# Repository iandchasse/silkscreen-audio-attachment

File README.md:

# Silkscreen audio attachment

> [!IMPORTANT]
> **AI-generated design. This is an accessory, not part of the Silkscreen PCBA.**
>
> This audio attachment was designed with substantial AI assistance: its board and housing are generated by code
> written with AI tools. The Silkscreen PCBA itself ([silkscreen-pcb](https://github.com/iandchasse/silkscreen-pcb))
> was not AI-generated. See Silkscreen's AI disclosure: https://silkscreenreader.com/ai

**A clip-on headphone / line output for the [Silkscreen](https://github.com/iandchasse/silkscreen-pcb) e-reader.**
It is a small cap that pushes onto the top of the 4.26" case, the same way as the
[light attachment](https://github.com/iandchasse/silkscreen-light-attachment). Six header pins go down through the opening the case already has
in its top wall and plug into the main board's expansion header, the 12-pin socket on its top edge (`J6`). The case
is not modified. A 3.5 mm stereo jack sits at the cap's left end, as seen from the display side.

> **Status (2026-11-09): rev A, designed and checked in CAD. NOT built or tested.**
> - **Board:** passes ERC 0 and DRC 0 with schematic parity, plus its own pin-position, keep-out, silk and field gates.
> - **Printed parts:** pass every scripted fit check against the current 4.26" standard case.
> - **First article:** see [docs/ASSEMBLY.md](docs/ASSEMBLY.md) "First power-up". Meter the jack's tip/ring/sleeve
>   mapping before plugging in headphones.

## How it works
- **Signals:**
  - The e-reader sends audio as I2S on the expansion header's three spare GPIOs: bit clock on `IO46` (pin 2), data on
    `IO45` (pin 3), word select on `IO3` (pin 9).
  - No master clock, no I2C, no setup registers.
- **Audio path:** a TI **PCM5102A** DAC drives a TI **TPA6138A2** ground-centred headphone driver, which drives the
  jack (tip = left, ring = right, sleeve = ground).
  - About 40 mW into 32 Ω.
  - About 2 Vrms into a line input.
- **Power:**
  - It comes from the battery pin (pin 12) through a TI **TPS7A2033** 3.3 V regulator.
  - The regulator only turns on while audio is playing: a two-diode charge pump on the word-select line drives its
    enable pin.
  - When the e-reader stops sending audio, the headphone driver mutes after about 1 s and the whole board switches off
    after about 2-4 s.
  - Idle draw is about 0.1 µA. The board never uses the header's 3V3 pin, which is limited to 20 mA on Rev 1.03.
- **Draw while playing:** about 33 mA in silence, about 50 mA at normal headphone level, about 110 mA at full volume
  into 32 Ω.
- **Presence detect:** the firmware can tell whether the cap is fitted.
  - It turns on `IO3`'s internal pull-up and reads the pin. The cap's 10 kΩ pull-down (`R7`) makes it read LOW.
  - With no cap, or with the light attachment (which has no pin 9), it reads HIGH.
- **Firmware:** the e-reader firmware needs I2S output added; it is not in the current firmware.
  - See [docs/FIRMWARE-NOTES.md](docs/FIRMWARE-NOTES.md) for the settings, the presence check and a tone-test example.
  - An existing CrossPoint fork already has an audio player (MP3, FLAC, AAC, Opus...) that can be ported with a few
    changes. [research/software.md](research/software.md) covers it, along with text-to-speech options and what the
    output should sound like: about phone-headphone-jack quality, against the 16 kHz "phone call" sound of some other
    e-readers.
- **Bluetooth:** not on the board.
  - The ESP32-S3 can't send Bluetooth headphone audio itself.
  - The one no-firmware module found is unverified, and JLC can't assemble it.
  - **A battery-powered 3.5 mm Bluetooth transmitter plugged into the jack works today.** See
    [docs/BLUETOOTH-FOLLOWUP.md](docs/BLUETOOTH-FOLLOWUP.md).

## What you need
| Item | Qty | Notes |
|---|---|---|
| Audio PCBA | 1 | 2 layers, 1.0 mm, 65.0 × 13.0 mm. JLCPCB assembles the 42 SMD parts on the top side. See [docs/ORDERING.md](docs/ORDERING.md) |
| Pin header 1 × 4, 11.5 mm (Hong Cheng HC-PZ254-11.5L-1x4PZ) | 1 | [LCSC C27985189](https://www.lcsc.com/product-detail/C27985189.html), soldered by you (`J1`, pins 1-4) |
| Pin header 1 × 1, 11.5 mm (Hong Cheng HC-PZ254-11.5L-1x1PZ) | 2 | [LCSC C27985186](https://www.lcsc.com/product-detail/C27985186.html), soldered by you (`J2` on pin 9, `J3` on pin 12) |
| Printed base and lid | 1 each | PETG (PLA for a trial), no supports. Base 20 min 21 s / 3.25 g; lid 12 min 36 s / 3.39 g (OrcaSlicer, 0.4 nozzle, 0.20 mm). Turn on "Detect thin wall" so the 0.2 mm stop under each screw hole prints |
| M2 × 3 pan-head screws | 2 | No longer than 3 mm |

Any standard 2.54 mm breakaway male header with 11.5 mm pins also works for the headers: 6.0 mm mating side, 2.5 mm
body and 3.0 mm tail. These are the same pins as the light attachment uses. Snap a 1 × 4 and two 1 × 1 pieces off a
strip.

**Cost:** about $41 for 5 assembled boards at JLCPCB (about $8 each), before shipping. Most of a small order is JLC's
fixed fees (about $25). See [docs/ORDERING.md](docs/ORDERING.md).

## Safety
- **Only these header pins have metal:** 1 and 4 (ground), 2, 3, 9 (I2S) and 12 (battery). The light pins (5, 6, 11),
  3V3 (7) and I2C (8, 10) have nothing on this board.
- **Plug it in only with the cap assembled.** The cap keys the pins: it only fits one way, and turned round the pins
  land on solid plastic. A bare board can be pushed in wrongly and would put the battery pin on the wrong pins.
- **All three audio lines are ESP32-S3 boot strapping pins.** `IO45` held HIGH at reset stops the e-reader booting;
  `IO46` HIGH breaks download mode; `IO3` only matters if a JTAG eFuse is burned.
  - The board only pulls them LOW, which is the correct level: 100 kΩ on `IO45`/`IO46` and 10 kΩ on `IO3`.
  - Nothing on it can drive a line HIGH.
  - Still, run the boot check in [docs/ASSEMBLY.md](docs/ASSEMBLY.md) on a first board.
- **While USB charges and audio plays,** the charger can't finish charging, because the board draws more than its
  termination current. Charging finishes normally a few seconds after the audio stops.
- **Volume:** the hardware has no volume control. Start the firmware at about -30 dBFS for headphones.

## Folders
| Path | What |
|---|---|
| `pcb/` | Generated KiCad 9 project (`pcb/tools/` builds everything; don't hand-edit the `.kicad_*` files). Fab files in `pcb/production/` |
| `housing/` | CadQuery project for the base and lid, its fit checks and print files (`housing/out/print/`) |
| `design/DESIGN-SPEC.md` | The design contract and the decisions behind it |
| `research/` | Audio chain, power, Bluetooth and software research (existing firmware, libraries, TTS, sound quality); `basis/` holds the J6 and case notes from the light attachment |
| `docs/` | Ordering, assembly, firmware notes, Bluetooth follow-up |

## Regenerating
**Board** (close KiCad first):
```
cd pcb
"C:\Program Files\KiCad\9.0\bin\python.exe" tools\generate.py --reroute
"C:\Program Files\KiCad\9.0\bin\python.exe" tools\make_outputs.py
```
- `generate.py` places the parts and routes the board; that takes about 10 min, up to 40 seeded attempts, stopping at
  the first with 0 failures.
- `make_outputs.py` writes production files only if every gate passes.

**Housing**, with the enclosure project's venv (CadQuery, trimesh, manifold3d):
```
cd housing\src
"..\..\..\silkscreen-enclosure-claude\.venv\Scripts\python.exe" build.py
```
- It reads `pcb/build/geometry.json`, the E-frame PCBA STL, and the case meshes in
  `../silkscreen-enclosures/enclosures/case-426/out/standard` (override with `SILKSCREEN_CASE_OUT`).
- The 3.68" case has no expansion header and isn't supported.

## Licence
CERN-OHL-S v2; see [LICENSE](LICENSE) and [NOTICE](NOTICE).

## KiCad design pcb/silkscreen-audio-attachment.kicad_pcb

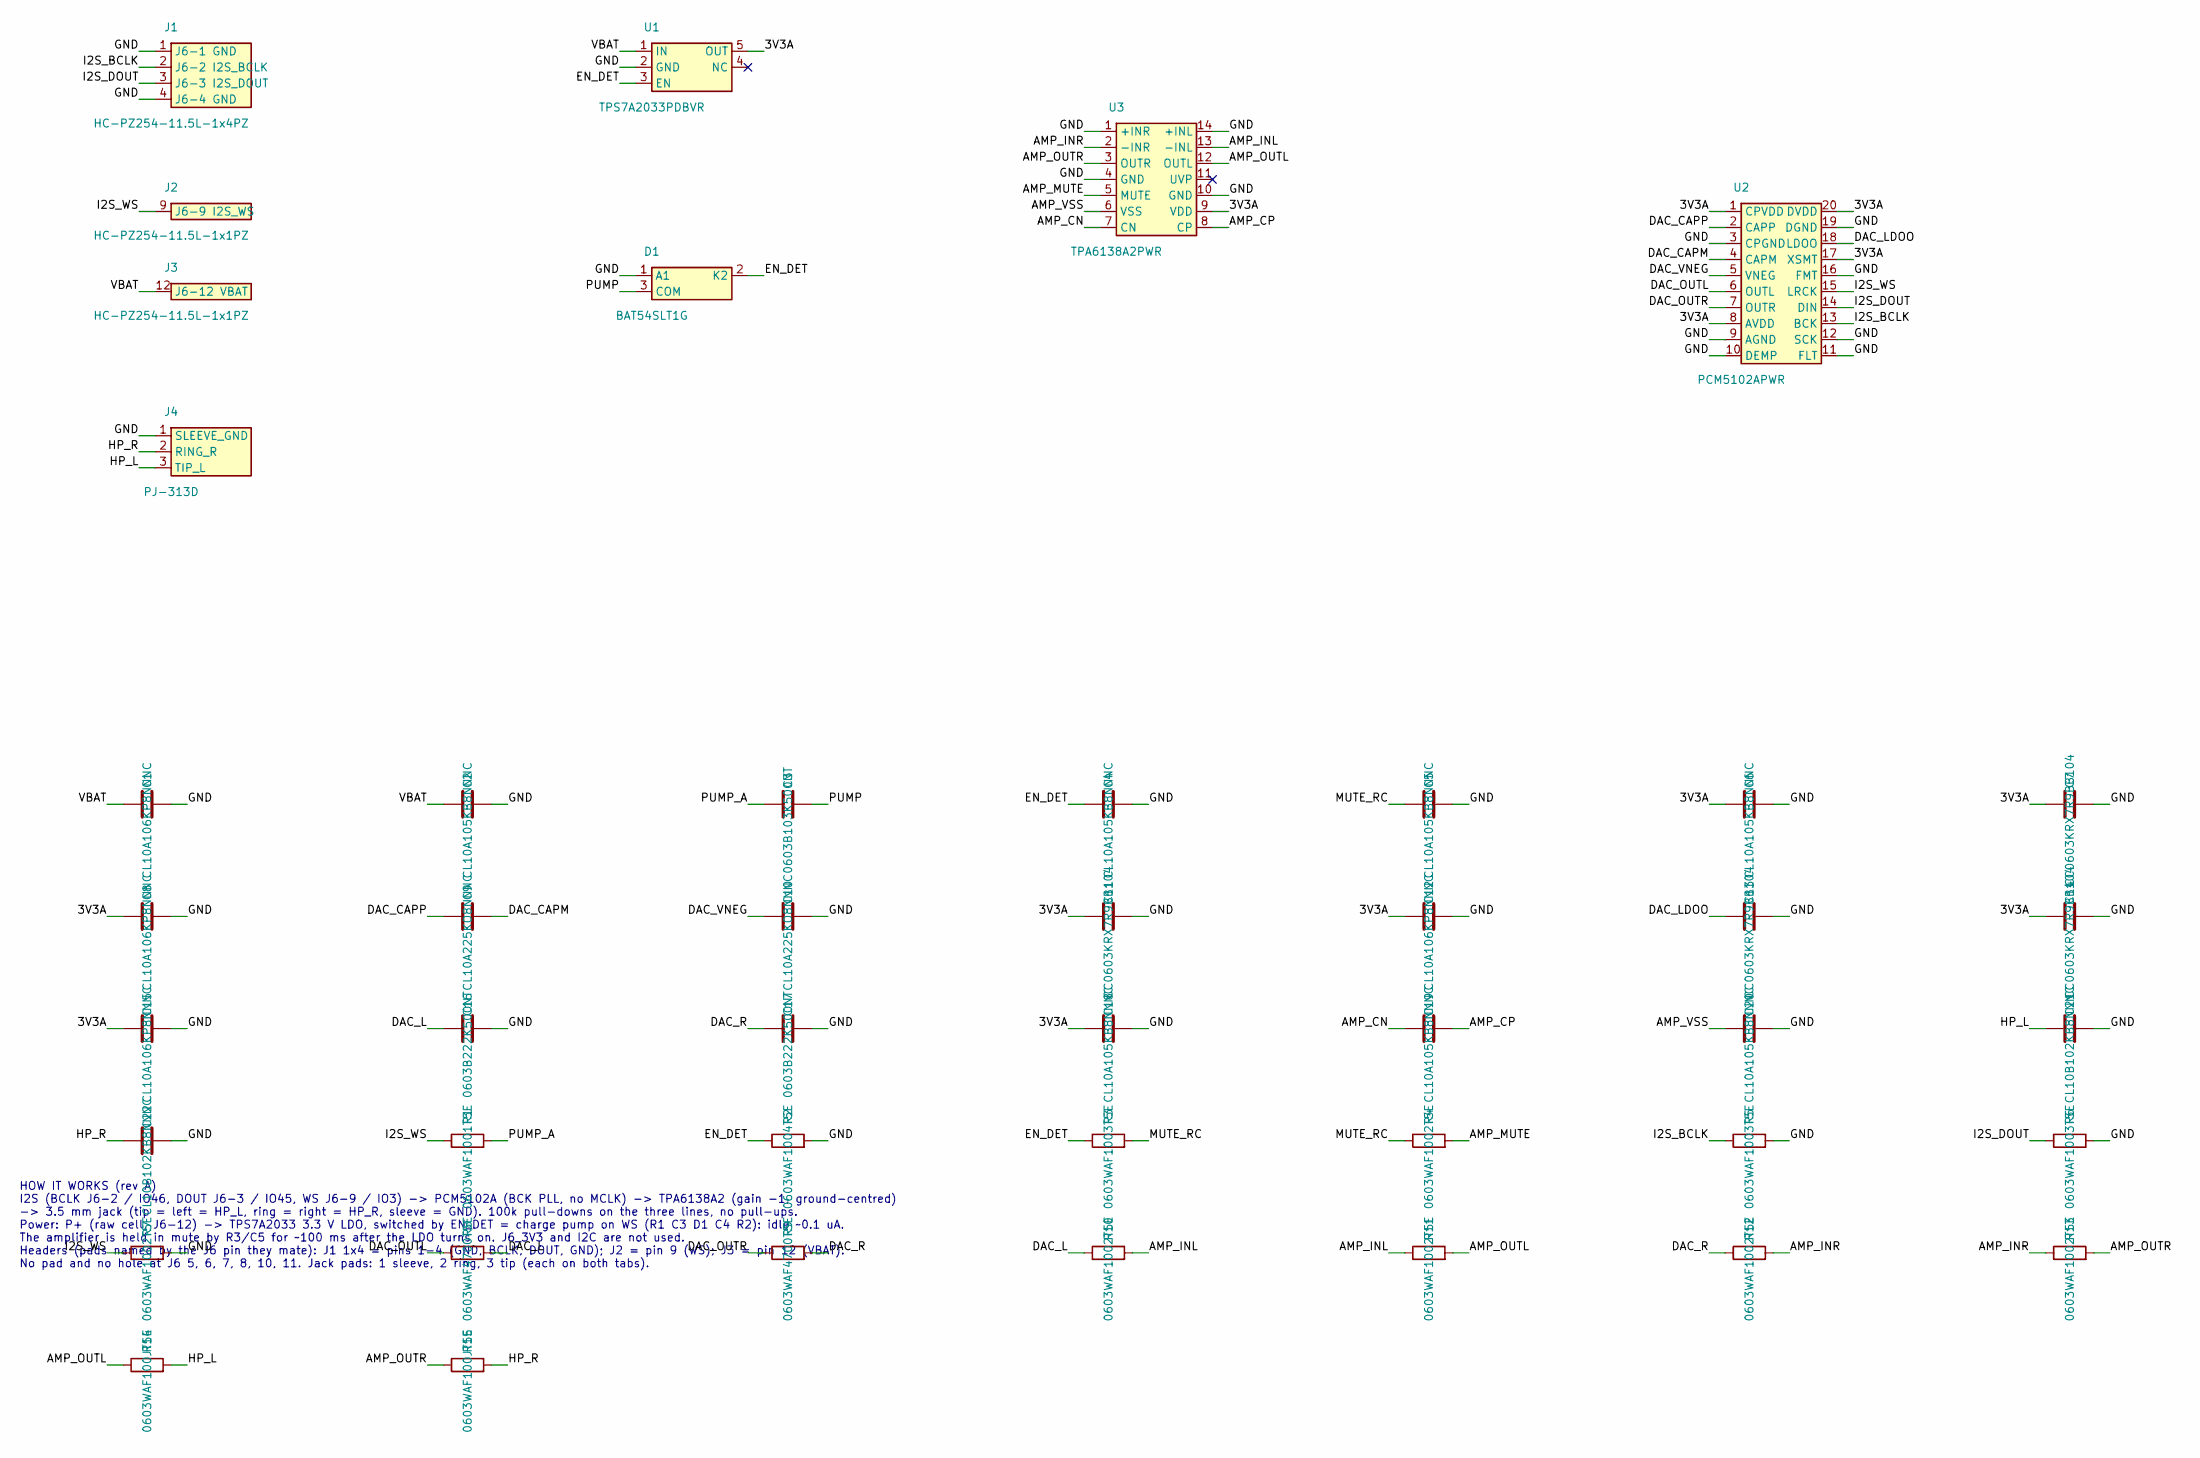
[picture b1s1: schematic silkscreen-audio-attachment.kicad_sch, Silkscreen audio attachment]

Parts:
C1, C8, C12, C15: CL10A106KP8NNNC; C_0603_1608Metric; MPN CL10A106KP8NNNC; DigiKey search DigiKey for CL10A106KP8NNNC (par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
C2, C4, C5, C6, C18, C19, C20: CL10A105KB8NNNC; C_0603_1608Metric; MPN CL10A105KB8NNNC; DigiKey search DigiKey for CL10A105KB8NNNC (par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
C3: 0603B103K500NT; C_0603_1608Metric; MPN 0603B103K500NT; DigiKey search DigiKey for 0603B103K500NT (part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
C7, C11, C13, C14: CC0603KRX7R9BB104; C_0603_1608Metric; MPN CC0603KRX7R9BB104; DigiKey search DigiKey for CC0603KRX7R9BB104 (p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
C9, C10: CL10A225KO8NNNC; C_0603_1608Metric; MPN CL10A225KO8NNNC; DigiKey search DigiKey for CL10A225KO8NNNC (par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
C16, C17: 0603B222K500NT; C_0603_1608Metric; MPN 0603B222K500NT; DigiKey search DigiKey for 0603B222K500NT (part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
C21, C22: CL10B102KB8NNNC; C_0603_1608Metric; MPN CL10B102KB8NNNC; DigiKey search DigiKey for CL10B102KB8NNNC (par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
D1: BAT54SLT1G; SOT-23; MPN BAT54SLT1G; DigiKey BAT54SLT1GOSCT-ND
J1: HC-PZ254-11.5L-1x4PZ; J6_PLUG_1x4_P1-P4; MPN HC-PZ254-11.5L-1x4PZ; DigiKey n/a - Hong Cheng is LCSC-only; DigiKey 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
J2: HC-PZ254-11.5L-1x1PZ; J6_PLUG_1x1_P9; MPN HC-PZ254-11.5L-1x1PZ; DigiKey 1 pin cut from a Harwin M20-999 series 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
J3: HC-PZ254-11.5L-1x1PZ; J6_PLUG_1x1_P12; MPN HC-PZ254-11.5L-1x1PZ; DigiKey 1 pin cut from a Harwin M20-999 series 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
J4: PJ-313D; JACK_3.5mm_SHOUHAN_PJ-313D; MPN PJ-313D; DigiKey none (LCSC only); DigiKey alternative w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
R1: 0603WAF1001T5E; R_0603_1608Metric; MPN 0603WAF1001T5E; DigiKey search DigiKey for 0603WAF1001T5E (part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
R2: 0603WAF1004T5E; R_0603_1608Metric; MPN 0603WAF1004T5E; DigiKey search DigiKey for 0603WAF1004T5E (part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
R3, R5, R6: 0603WAF1003T5E; R_0603_1608Metric; MPN 0603WAF1003T5E; DigiKey search DigiKey for 0603WAF1003T5E (part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
R4, R7, R10, R11, R12, R13: 0603WAF1002T5E; R_0603_1608Metric; MPN 0603WAF1002T5E; DigiKey search DigiKey for 0603WAF1002T5E (part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
R8, R9: 0603WAF4700T5E; R_0603_1608Metric; MPN 0603WAF4700T5E; DigiKey search DigiKey for 0603WAF4700T5E (part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
R14, R15: 0603WAF100JT5E; R_0603_1608Metric; MPN 0603WAF100JT5E; DigiKey search DigiKey for 0603WAF100JT5E (part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
U1: TPS7A2033PDBVR; SOT-23-5; MPN TPS7A2033PDBVR; DigiKey 296-TPS7A2033PDBVRCT-ND
U2: PCM5102APWR; TSSOP-20_4.4x6.5mm_P0.65mm; MPN PCM5102APWR; DigiKey 296-36707-1-ND
U3: TPA6138A2PWR; TSSOP-14_4.4x5mm_P0.65mm; MPN TPA6138A2PWR; DigiKey 296-28248-1-ND

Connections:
/3V3A: C6.1, C7.1, C8.1, C11.1, C12.1, C14.1, C15.1, C18.1, U1.5 (OUT), U2.1 (CPVDD), U2.8 (AVDD), U2.17 (XSMT), U2.20 (DVDD), U3.9 (VDD)
/AMP_CN: C19.1, U3.7 (CN)
/AMP_CP: C19.2, U3.8 (CP)
/AMP_INL: R10.2, R11.1, U3.13 (-INL)
/AMP_INR: R12.2, R13.1, U3.2 (-INR)
/AMP_MUTE: R4.2, U3.5 (MUTE)
/AMP_OUTL: R11.2, R14.1, U3.12 (OUTL)
/AMP_OUTR: R13.2, R15.1, U3.3 (OUTR)
/AMP_VSS: C20.1, U3.6 (VSS)
/DAC_CAPM: C9.2, U2.4 (CAPM)
/DAC_CAPP: C9.1, U2.2 (CAPP)
/DAC_L: C16.1, R8.2, R10.1
/DAC_LDOO: C13.1, U2.18 (LDOO)
/DAC_OUTL: R8.1, U2.6 (OUTL)
/DAC_OUTR: R9.1, U2.7 (OUTR)
/DAC_R: C17.1, R9.2, R12.1
/DAC_VNEG: C10.1, U2.5 (VNEG)
/EN_DET: C4.1, D1.2 (K2), R2.1, R3.1, U1.3 (EN)
/GND: C1.2, C2.2, C4.2, C5.2, C6.2, C7.2, C8.2, C10.2, C11.2, C12.2, C13.2, C14.2, C15.2, C16.2, C17.2, C18.2, C20.2, C21.2, C22.2, D1.1 (A1), J1.1 (J6-1 GND), J1.4 (J6-4 GND), J4.1 (SLEEVE_GND), R2.2, R5.2, R6.2, R7.2, U1.2 (GND), U2.3 (CPGND), U2.9 (AGND), U2.10 (DEMP), U2.11 (FLT), U2.12 (SCK), U2.16 (FMT), U2.19 (DGND), U3.1 (+INR), U3.4 (GND), U3.10 (GND), U3.14 (+INL)
/HP_L: C21.1, J4.3 (TIP_L), R14.2
/HP_R: C22.1, J4.2 (RING_R), R15.2
/I2S_BCLK: J1.2 (J6-2 I2S_BCLK), R5.1, U2.13 (BCK)
/I2S_DOUT: J1.3 (J6-3 I2S_DOUT), R6.1, U2.14 (DIN)
/I2S_WS: J2.9, R1.1, R7.1, U2.15 (LRCK)
/MUTE_RC: C5.1, R3.2, R4.1
/PUMP: C3.2, D1.3 (COM)
/PUMP_A: C3.1, R1.2
/VBAT: C1.1, C2.1, J3.12, U1.1 (IN)

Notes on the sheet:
HOW IT WORKS (rev A) I2S (BCLK J6-2 / IO46, DOUT J6-3 / IO45, WS J6-9 / IO3) -> PCM5102A (BCK PLL, no MCLK) -> TPA6138A2 (gain -1, ground-centred) -> 3.5 mm jack (tip = left = HP_L, ring = right = HP_R, sleeve = GND). 100k pull-downs on the three lines, no pull-ups. Power: P+ (raw cell, J6-12) -> T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

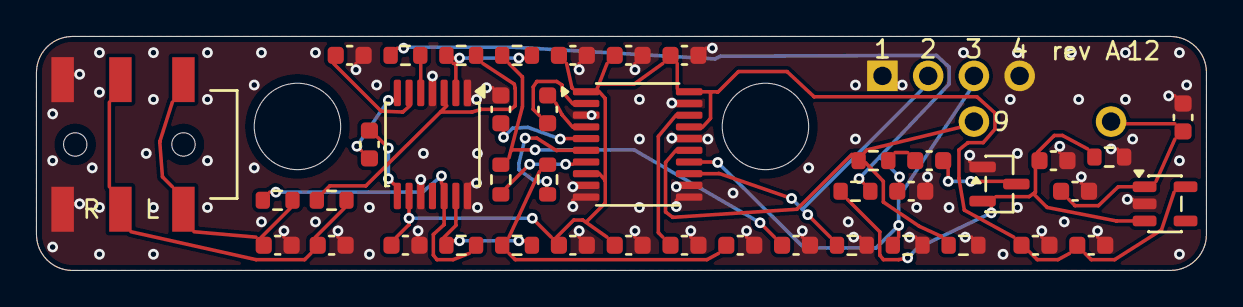
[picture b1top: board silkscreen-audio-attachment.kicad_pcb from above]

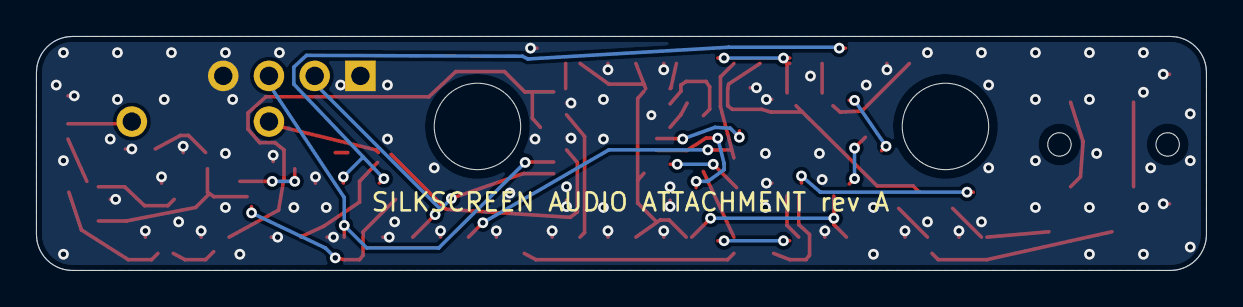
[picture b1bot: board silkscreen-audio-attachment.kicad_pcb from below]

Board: 2 copper layers, 65.0 x 13.0 mm, 47 parts (3 on the bottom side), 28 nets.

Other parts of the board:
H1: M1 lid screw column (rev C base, left boss moved 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; NPTH_4.80mm
H2: M2 lid screw column; NPTH_4.80mm

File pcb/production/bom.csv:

Qty,Refs,Value,Manufacturer,MPN,DigiKey,LCSC,JLC type,Footprint,Assembly,Description
4,"C1,C8,C12,C15",CL10A106KP8NNNC,Samsung Electro-Mechanics,CL10A106KP8NNNC,search DigiKey for CL10A106KP8NNNC (part number not verified),C19702,JLC Basic,C_0603_1608Metric,JLC SMT (top side),10 uF 10 V X5R 0603
7,"C2,C4,C5,C6,C18,C19,C20",CL10A105KB8NNNC,Samsung Electro-Mechanics,CL10A105KB8NNNC,search DigiKey for CL10A105KB8NNNC (part number not verified),C15849,JLC Basic,C_0603_1608Metric,JLC SMT (top side),1 uF 50 V X5R 0603
1,C3,0603B103K500NT,Fenghua (FH),0603B103K500NT,search DigiKey for 0603B103K500NT (part number not verified),C57112,JLC Basic,C_0603_1608Metric,JLC SMT (top side),10 nF 50 V X7R 0603
4,"C7,C11,C13,C14",CC0603KRX7R9BB104,Yageo,CC0603KRX7R9BB104,search DigiKey for CC0603KRX7R9BB104 (part number not verified),C14663,JLC Basic,C_0603_1608Metric,JLC SMT (top side),100 nF 50 V X7R 0603
2,"C9,C10",CL10A225KO8NNNC,Samsung Electro-Mechanics,CL10A225KO8NNNC,search DigiKey for CL10A225KO8NNNC (part number not verified),C23630,JLC Basic,C_0603_1608Metric,JLC SMT (top side),2.2 uF 16 V X5R 0603
2,"C16,C17",0603B222K500NT,Fenghua (FH),0603B222K500NT,search DigiKey for 0603B222K500NT (part number not verified),C1604,JLC Basic,C_0603_1608Metric,JLC SMT (top side),2.2 nF 50 V X7R 0603
2,"C21,C22",CL10B102KB8NNNC,Samsung Electro-Mechanics,CL10B102KB8NNNC,search DigiKey for CL10B102KB8NNNC (part number not verified),C1588,JLC Basic,C_0603_1608Metric,JLC SMT (top side),1 nF 50 V X7R 0603
1,D1,BAT54SLT1G,onsemi,BAT54SLT1G,BAT54SLT1GOSCT-ND,C8592,JLC Extended,SOT-23,JLC SMT (top side),"Dual Schottky diode, series pair, SOT-23. JLC/LCSC part: Jiangsu Changjing BAT54S (C8592)"
1,J1,HC-PZ254-11.5L-1x4PZ,Hong Cheng,HC-PZ254-11.5L-1x4PZ,"n/a - Hong Cheng is LCSC-only; DigiKey equivalent: Harwin M20-999 series 1x4 cut from a longer strip (6.1 mm post, 3 mm tail), part number not verified",C27985189,JLC Extended,J6_PLUG_1x4_P1-P4,"THT: JLC hand-solders it, or untick it at JLC and solder it yourself","1x4 2.54 mm straight male pin header, body 2.5, mating post 6.0, tail 3.0, 0.64 sq; mounted from the underside, soldered by the builder on the top side; pins = J6 1/2/3/4"
1,J2,HC-PZ254-11.5L-1x1PZ,Hong Cheng,HC-PZ254-11.5L-1x1PZ,"1 pin cut from a Harwin M20-999 series strip (6.1 mm post, 3 mm tail), part number not verified",C27985186,JLC Extended,J6_PLUG_1x1_P9,"THT: JLC hand-solders it, or untick it at JLC and solder it yourself","1x1 2.54 mm straight male pin header, body 2.5, mating post 6.0, tail 3.0, 0.64 sq; mounted from the underside, soldered by the builder on the top side; pins = J6 9"
1,J3,HC-PZ254-11.5L-1x1PZ,Hong Cheng,HC-PZ254-11.5L-1x1PZ,"1 pin cut from a Harwin M20-999 series strip (6.1 mm post, 3 mm tail), part number not verified",C27985186,JLC Extended,J6_PLUG_1x1_P12,"THT: JLC hand-solders it, or untick it at JLC and solder it yourself","1x1 2.54 mm straight male pin header, body 2.5, mating post 6.0, tail 3.0, 0.64 sq; mounted from the underside, soldered by the builder on the top side; pins = J6 12"
1,J4,PJ-313D,SHOU HAN,PJ-313D,none (LCSC only); DigiKey alternative with a different land: CUI SJ-3524-SMT-TR,C668608,JLC Extended,JACK_3.5mm_SHOUHAN_PJ-313D,JLC SMT (top side),"3.5 mm stereo headphone jack, SMD, 14 x 6 x 5 mm; pad 1 sleeve (GND), 2 ring (HP_R), 3 tip (HP_L); both tabs of a contact share the pad number"
1,R1,0603WAF1001T5E,UNI-ROYAL,0603WAF1001T5E,search DigiKey for 0603WAF1001T5E (part number not verified),C21190,JLC Basic,R_0603_1608Metric,JLC SMT (top side),1 kOhm 1 % 0603
1,R2,0603WAF1004T5E,UNI-ROYAL,0603WAF1004T5E,search DigiKey for 0603WAF1004T5E (part number not verified),C22935,JLC Basic,R_0603_1608Metric,JLC SMT (top side),1 MOhm 1 % 0603
3,"R3,R5,R6",0603WAF1003T5E,UNI-ROYAL,0603WAF1003T5E,search DigiKey for 0603WAF1003T5E (part number not verified),C25803,JLC Basic,R_0603_1608Metric,JLC SMT (top side),100 kOhm 1 % 0603
6,"R4,R7,R10,R11,R12,R13",0603WAF1002T5E,UNI-ROYAL,0603WAF1002T5E,search DigiKey for 0603WAF1002T5E (part number not verified),C25804,JLC Basic,R_0603_1608Metric,JLC SMT (top side),10 kOhm 1 % 0603
2,"R8,R9",0603WAF4700T5E,UNI-ROYAL,0603WAF4700T5E,search DigiKey for 0603WAF4700T5E (part number not verified),C23179,JLC Basic,R_0603_1608Metric,JLC SMT (top side),470 Ohm 1 % 0603
2,"R14,R15",0603WAF100JT5E,UNI-ROYAL,0603WAF100JT5E,search DigiKey for 0603WAF100JT5E (part number not verified),C22859,JLC Basic,R_0603_1608Metric,JLC SMT (top side),10 Ohm 0603
1,U1,TPS7A2033PDBVR,Texas Instruments,TPS7A2033PDBVR,296-TPS7A2033PDBVRCT-ND,C2862740,JLC Extended,SOT-23-5,JLC SMT (top side),"3.3 V 300 mA ultra-low-noise LDO with enable, SOT-23-5"
1,U2,PCM5102APWR,Texas Instruments,PCM5102APWR,296-36707-1-ND,C107671,JLC Extended,TSSOP-20_4.4x6.5mm_P0.65mm,JLC SMT (top side),"112 dB stereo audio DAC, 32-bit 384 kHz I2S, BCK PLL (no MCLK), TSSOP-20"
1,U3,TPA6138A2PWR,Texas Instruments,TPA6138A2PWR,296-28248-1-ND,C183097,JLC Extended,TSSOP-14_4.4x5mm_P0.65mm,JLC SMT (top side),"DirectPath ground-centred stereo headphone amplifier, TSSOP-14"

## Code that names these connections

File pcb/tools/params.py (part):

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        datasheet="https://www.ti.com/lit/ds/symlink/tps7a20.pdf",
        desc="3.3 V 300 mA ultra-low-noise LDO with enable, SOT-23-5",
        left=[("1", "IN"), ("2", "GND"), ("3", "EN")], right=[("5", "OUT"), ("4", "NC")],
        pins={"1": "VBAT", "2": "GND", "3": "EN_DET", "4": None, "5": "3V3A"}),
    "U2": dict(
        fp="TSSOP-20", sym="PCM5102A", value="PCM5102APWR", manufacturer="Texas Instruments", mpn="PCM5102APWR",
        digikey="296-36707-1-ND", lcsc="C107671", stock=1284,
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              ("8", "AVDD"), ("9", "AGND"), ("10", "DEMP")],
        right=[("20", "DVDD"), ("19", "DGND"), ("18", "LDOO"), ("17", "XSMT"), ("16", "FMT"), ("15", "LRCK"), ("14", "DIN"),
               ("13", "BCK"), ("12", "SCK"), ("11", "FLT")],
        pins={"1": "3V3A", "2": "DAC_CAPP", "3": "GND", "4": "DAC_CAPM", "5": "DAC_VNEG", "6": "DAC_OUTL", "7": "DAC_OUTR",
              "8": "3V3A", "9": "GND", "10": "GND", "11": "GND", "12": "GND", "13": "I2S_BCLK", "14": "I2S_DOUT",
              "15": "I2S_WS", "16": "GND", "17": "3V3A", "18": "DAC_LDOO", "19": "GND", "20": "3V3A"}),
    "U3": dict(
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        desc="DirectPath ground-centred stereo headphone amplifier, TSSOP-14",
        left=[("1", "+INR"), ("2", "-INR"), ("3", "OUTR"), ("4", "GND"), ("5", "MUTE"), ("6", "VSS"), ("7", "CN")],
        right=[("14", "+INL"), ("13", "-INL"), ("12", "OUTL"), ("11", "UVP"), ("10", "GND"), ("9", "VDD"), ("8", "CP")],
        pins={"1": "GND", "2": "AMP_INR", "3": "AMP_OUTR", "4": "GND", "5": "AMP_MUTE", "6": "AMP_VSS", "7": "AMP_CN",
              "8": "AMP_CP", "9": "3V3A", "10": "GND", "11": None, "12": "AMP_OUTL", "13": "AMP_INL", "14": "GND"}),
    "D1": dict(
        fp="SOT-23", sym="BAT54S", value="BAT54SLT1G", manufacturer="onsemi", mpn="BAT54SLT1G",
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        datasheet="https://www.onsemi.com/pdf/datasheet/bat54slt1-d.pdf",
        desc="Dual Schottky diode, series pair, SOT-23. JLC/LCSC part: Jiangsu Changjing BAT54S (C8592)",
        left=[("1", "A1"), ("3", "COM")], right=[("2", "K2")],
        pins={"1": "GND", "2": "EN_DET", "3": "PUMP"}),
}
# NC pins carry a no-connect flag in the schematic
FP_LIB = {"SOT-23-5": ("Package_TO_SOT_SMD", "SOT-23-5"), "SOT-23": ("Package_TO_SOT_SMD", "SOT-23"),
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

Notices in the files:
pcb/silkscreen-audio-attachment.kicad_pcb:
Licensed under CERN-OHL-S-2.0
(c) 2026 idc LLC
